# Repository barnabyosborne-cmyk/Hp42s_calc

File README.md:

# HP-42S clone — Plus42 on an ESP32-S3

An HP-42S-shaped calculator: e-paper display, LiPo cell, USB-C and BLE, a
custom keypad PCB with metal dome switches, a resin-printed case, running
[Plus42](https://thomasokken.com/plus42/) on an ESP32-S3.

Case dimensions follow the original HP-42S as closely as the parts allow:
**148 × 80 × 15 mm**.

## What is in here

| Path | What it is |
|---|---|
| `elec/src/*.ato` | The wiring, as [atopile](https://atopile.io) source. Compiles to a netlist. |
| `elec/footprints/hp42s.pretty/` | The footprints KiCad does not ship, generated by the two scripts in `tools/`. |
| `elec/layout/` | The KiCad project. Placement and routing live here. |
| `tools/gen_dome_footprints.py` | Parametric generator for the metal dome sites. |
| `tools/gen_ic_footprints.py` | The same for the regulator, the IR emitter, the status LED, the ESD array, the USB-C receptacle and the recovery buttons. |
| `docs/connections.md` | The connection table in prose, with the reasoning. |
| `docs/keypad-geometry.md` | The measured key grid, and the clearances that follow. |
| `docs/display-mounting.md` | The panel's tail and off-centre image, and where the cell can go. |
| `docs/front-face.md` | The etched metal plate, the window, and an edge-lit frontlight. |
| `docs/before-layout.md` | **What is still open, and whether it stops you starting.** |
| `docs/board-thickness.md` | Why the board is 1.6 mm, and flex under the keyboard. |
| `docs/layout-walkthrough.md` | **The layout, step by step.** Written for a first PCB. |
| `docs/pcb-process.md` | The map from netlist to boards in your hand. |
| `docs/kicad-setup.md` | Why the pin numbers are what they are. |
| `docs/breadboard.md` | What a XIAO ESP32-S3 and a spare Waveshare panel can and cannot prove. |
| `firmware/` | The Plus42 port. Not started. |
| `hardware/` | Case and keycap files. Barnaby's own CAD. |

## Building the netlist

```
pip install atopile        # 0.2.69 at time of writing
ato --non-interactive build
```

The flag goes before `build`, not after.

Output lands in `build/`: `default.net` (KiCad netlist), `default.csv` (BOM),
and a designator map. atopile does the wiring and the netlist; it does **not**
place or route. Layout stays in KiCad.

## Headline choices

- **MCU** — ESP32-S3-MINI-1-N8. The S3 over the C3/C6 because only the S3 has
  full USB OTG, which is what allows drag-and-drop file transfer as a mass
  storage device. The `-N8` specifically: it has no PSRAM, and octal PSRAM
  would eat GPIO33–37, where the panel interface lives.
- **Display** — Good Display GDEY0266T90, 2.66", 296 × 152 px in a 71.82 ×
  36.30 mm outline. Plus42 character cells are 6 × 8 px, rendered **2× across
  and 3× down**, giving **24 columns × 6 rows** at very close to the original
  42S's character size. The obvious 2.9" panel is 79.0 mm wide and will not
  fit an 80 mm shell. See `docs/character-size.md` for why the scaling is not
  square.
- **Power** — BQ25185 charger with power path → TPS63900 buck-boost to 3.3 V →
  MAX17048 fuel gauge. The buck-boost is mandatory: the panel's VCI cannot
  take 4.2 V.
- **Keypad** — 37 keys, 6 columns × 7 rows, no diodes. Columns sit on
  RTC-capable GPIOs and wake the chip from deep sleep via `ext1`, so there is
  no scanner IC and no standing current. The physical grid is measured off a
  real 42S and is not uniform: 12.5 mm columns on the function rows, 15 mm
  across the numeric block.
- **On and off are keys, not a switch.** `EXIT/ON` wakes it and shift-`EXIT`
  sleeps it, the way a real 42S works. There is no power slider: the 3.3 V rail
  is always up and "off" is deep sleep at about 21 µA. Driving row 6 alone and
  arming `ext1` on column 0 alone makes `EXIT/ON` the only key that can wake it.
  `docs/power-control.md`.
- **Single-sided assembly.** Every part the fab house solders is on the back of
  the board. The front carries the panel, the 38 dome sites and the frontlight
  sliver's lands, all fitted afterwards. `docs/top-edge.md`.
- **Battery life** — roughly **15 months** on the 1600 mAh cell that fits, at
  2 h/day and 1500 keystrokes. About 33 hours of continuous execution. The cell
  is 6 × 45 × 55 mm, in board X 14–69 and Y 13–58 on the back.

## What is not settled

- **The panel's 47 µH inductor.** Named (Sumida CDRH2D18) but still on a
  stand-in land pattern, because the drawing has not turned up.

## Licence

The Plus42 firmware is GPLv2, and that carries over: anyone given or sold a
unit has to be able to get the source. Worth deciding on before the firmware
lands here.

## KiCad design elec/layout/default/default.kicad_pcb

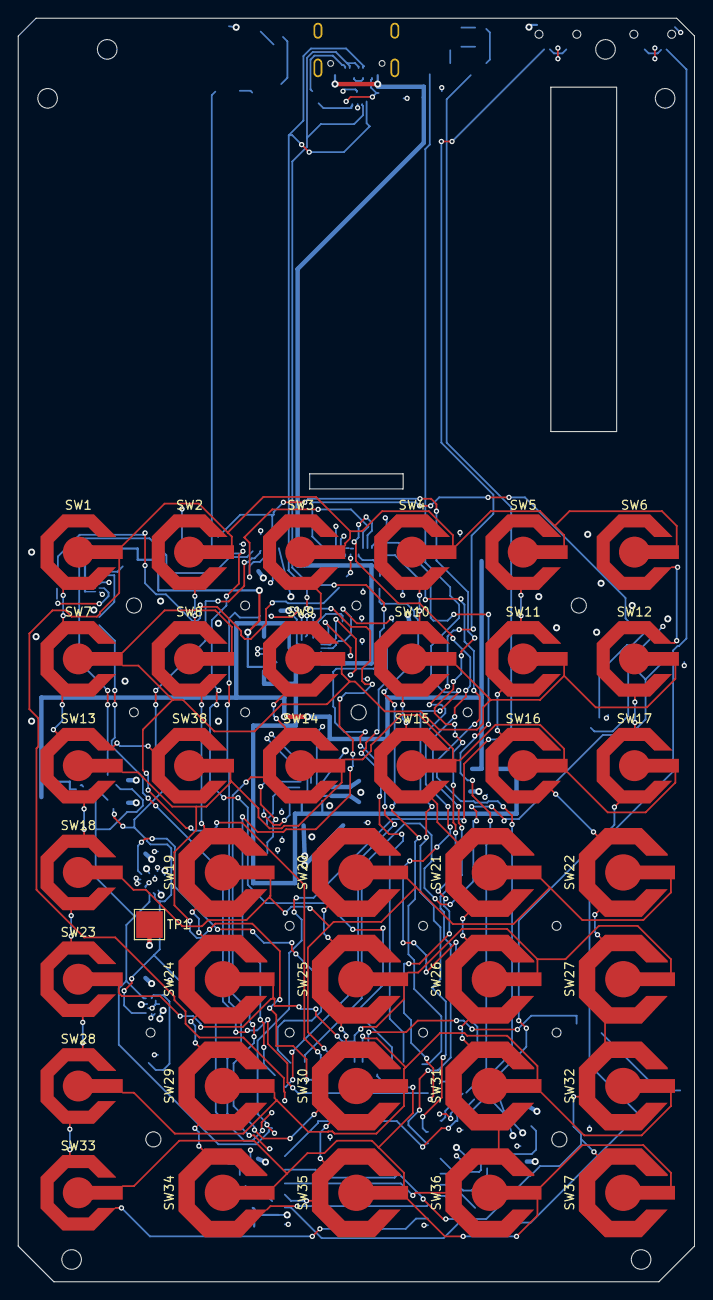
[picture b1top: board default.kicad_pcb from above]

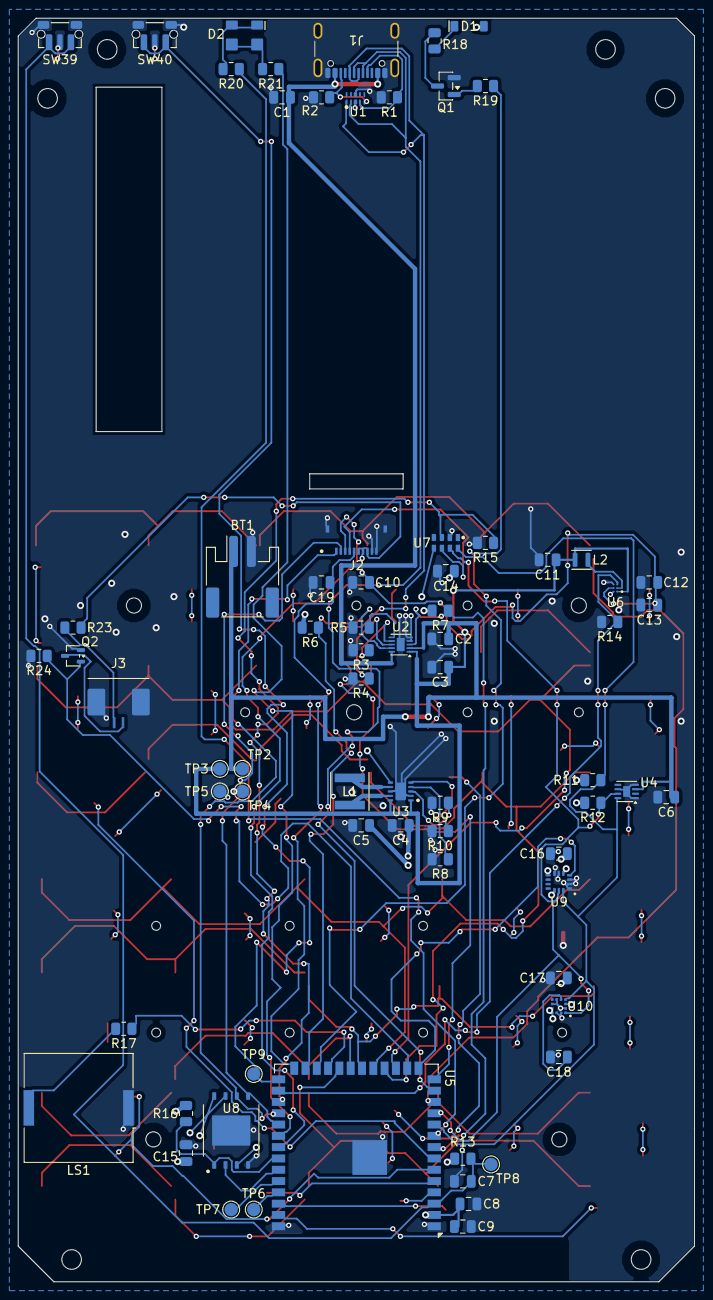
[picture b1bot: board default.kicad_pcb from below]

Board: 4 copper layers, 76.0 x 142.0 mm, 112 parts (73 on the bottom side), 64 nets.

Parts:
BT1: ?; JST_PH_S2B-PH-SM4-TB_1x02-1MP_P2.00mm_Horizontal
C1, C2, C3, C4, C5, C6, C7, C8, C9, C10, C11, C12, C13, C14, C15, C16, C17, C18, C19: ?; C_0805_2012Metric
D1: ?; Vishay_VSMB2943SLX01_SideView
D2: ?; XINGLIGHT_XL-C4040_SideView
J1: ?; USB_C_Receptacle_GCT_USB4105-xx-A_16P_TopMnt_Horizontal
J2: ?; Hirose_FH34SRJ-10S-0.5SH_1x10-1MP_P0.50mm_Horizontal
J3: ?; FPC_1.0mm_2P_TopContact_1.0K-LS
L1: ?; L_SXN_SMNR4020
L2: ?; L_Murata_DFE201610P
LS1: ?; Buzzer_Murata_PKLCS1212E
Q1: ?; SOT-23
Q2: ?; SOT-323_SC-70
R1, R2, R3, R4, R5, R6, R7, R8, R9, R10, R11, R12, R13, R14, R15, R16, R17, R18, R19, R20, R21, R23, R24: ?; R_0805_2012Metric
SW1, SW2, SW3, SW4, SW5, SW6, SW7, SW8, SW9, SW10, SW11, SW12, SW13, SW14, SW15, SW16, SW17, SW18, SW23, SW28, SW33, SW38: ?; Dome_4Leg_8.5mm
SW19, SW20, SW21, SW22, SW24, SW25, SW26, SW27, SW29, SW30, SW31, SW32, SW34, SW35, SW36, SW37: ?; Dome_4Leg_10mm
SW39, SW40: ?; Alps_SKRTLAE010_SidePush
TP1: ?; TestPoint_Pad_3.0x3.0mm
TP2, TP3, TP4, TP5, TP6, TP7, TP8, TP9: ?; TestPoint_Pad_D1.5mm
U1: ?; TI_DQA0010A_USON-10_2.5x1mm_P0.5mm
U2: ?; Texas_DSQ0010A_WSON-10-1EP_2x2mm_P0.4mm_EP0.9x1.5mm
U3: ?; TI_DSK0010A_WSON-10-1EP_2.5x2.5mm_P0.5mm_EP2x1.2mm
U4: ?; TDFN-8-1EP_2x2mm_P0.5mm_EP0.8x1.2mm
U5: ?; ESP32-S3-WROOM-1
U6: ?; TI_YFF0006_DSBGA-6_0.88x1.23mm_P0.4mm
U7: ?; MicroCrystal_C7_3.2x1.5mm_RV-8263
U8: ?; SPI_NAND_UPDFN-8_8x6mm_P1.27mm
U9: ?; ST_LGA-14L_3x2.5mm_P0.5mm
U10: ?; ST_LGA-12_2x2mm_P0.5mm

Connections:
bat: BT1.1, C2.1, C6.1, TP2.1, U2.2, U4.3
boot: SW40.1, TP9.1, U5.27
buzzer: R17.1, U5.23
c1: C18.1, U10.5
cathode: D1.1, R18.1
cc1: J1.A5, R1.1, U1.4
cc2: J1.B5, R2.1, U1.5
cfg1: R9.1, U3.3
cfg2: R10.1, U3.4
cfg3: R8.1, U3.5
chg_stat: R6.1, U2.9, U5.25
chg_stat2: R7.1, U2.3, U5.8
col0: SW1.1, SW7.1, SW13.1, SW18.1, SW23.1, SW28.1, SW33.1, SW38.1, U5.39
col1: SW2.1, SW8.1, SW19.1, SW24.1, SW29.1, SW34.1, U5.38
col2: SW3.1, SW9.1, SW14.1, SW20.1, SW25.1, SW30.1, SW35.1, U5.4
col3: SW4.1, SW10.1, SW15.1, SW21.1, SW26.1, SW31.1, SW36.1, U5.5
col4: SW5.1, SW11.1, SW16.1, SW22.1, SW27.1, SW32.1, SW37.1, U5.6
col5: SW6.1, SW12.1, SW17.1, U5.7
drain: Q1.3, R18.2
en: C7.1, R13.1, SW39.1, TP8.1, U5.3
extcomin: J2.4, U7.6
fl_a: J3.1, R23.2
fl_en: Q2.1, R24.1, U5.16
fl_k: J3.2, Q2.3
flash_cs: R16.1, U5.34, U8.1
flash_miso: U5.35, U8.2
gate: Q1.1, R19.2
gnd: BT1.2, C1.2, C2.2, C3.2, C4.2, C5.2, C6.2, C7.2, C8.2, C9.2, C10.2, C11.2, C12.2, C13.2, C14.2, C15.2, C16.2, C17.2, C18.2, C19.2, J1.A1, J1.A12, J1.B1, J1.B12, J1.SH, J2.9, J2.10, J2.MP, J3.MP, LS1.1, Q1.2, Q2.2, R1.2, R2.2, R3.2, R4.2, R5.2, R8.2, R9.2, R10.2, R14.2, R15.2, R24.2, SW39.2, SW39.MP, SW40.2, SW40.MP, TP1.1, TP5.1, U1.3, U1.8, U2.4, U2.5, U2.11, U3.2, U3.8, U3.11, U4.1, U4.4, U4.6, U4.9, U5.1, U5.40, U5.41, U6.A2, U6.C2, U7.2, U8.4, U8.9, U9.1, U9.2, U9.3, U9.6, U9.7, U10.2, U10.6, U10.8, U10.11, U10.12
i2c_scl: R12.1, U4.7, U5.11, U7.7, U9.13, U10.1
i2c_sda: R11.1, U4.8, U5.10, U7.8, U9.14, U10.4
ilim_vset: R3.1, U2.7
imu_int1: U5.15, U9.4
ir_led: R19.1, U5.24
iset: R4.1, U2.8
led_green: R21.1, U5.32
led_red: R20.1, U5.9
lx1: L1.1, U3.9
lx2: L1.2, U3.7
mip_clkoe: R15.1, U5.29, U7.3
mip_cs: J2.3, U5.33
mip_disp: C19.1, J2.5, U5.26
mip_mosi: J2.2, U5.31, U8.5
mip_pwr: R14.1, U5.28, U6.C1
mip_sck: J2.1, U5.30, U8.6
row0: SW1.2, SW2.2, SW3.2, SW4.2, SW5.2, SW6.2, U5.12
row1: SW7.2, SW8.2, SW9.2, SW10.2, SW11.2, SW12.2, U5.17
row2: SW13.2, SW14.2, SW15.2, SW16.2, SW17.2, SW38.2, U5.18
row3: SW18.2, SW19.2, SW20.2, SW21.2, SW22.2, U5.19
row4: SW23.2, SW24.2, SW25.2, SW26.2, SW27.2, U5.20
row5: SW28.2, SW29.2, SW30.2, SW31.2, SW32.2, U5.21
row6: SW33.2, SW34.2, SW35.2, SW36.2, SW37.2, U5.22
sounder: LS1.2, R17.2
sw5: L2.2, U6.B1
sys: C3.1, C11.1, L2.1, TP3.1, U2.1, U3.1, U3.10, U6.A1
t_green: D2.2, D2.4, R21.2
t_red: D2.1, D2.3, R20.2
ts_mr: R5.1, U2.6
uart0_rx: TP7.1, U5.36
uart0_tx: TP6.1, U5.37
usb_dm: J1.A7, J1.B7, U1.2, U5.13
usb_dp: J1.A6, J1.B6, U1.1, U5.14
v3v3: C4.1, C5.1, C8.1, C9.1, C14.1, C15.1, C16.1, C17.1, D1.2, R6.2, R7.2, R11.2, R12.2, R13.2, R16.2, TP4.1, U3.6, U5.2, U7.5, U8.3, U8.7, U8.8, U9.5, U9.8, U9.12, U10.3, U10.9, U10.10
v5: C10.1, C12.1, C13.1, J2.6, J2.7, J2.8, R23.1, U6.B2
vbus: C1.1, J1.A4, J1.A9, J1.B4, J1.B9, U2.10

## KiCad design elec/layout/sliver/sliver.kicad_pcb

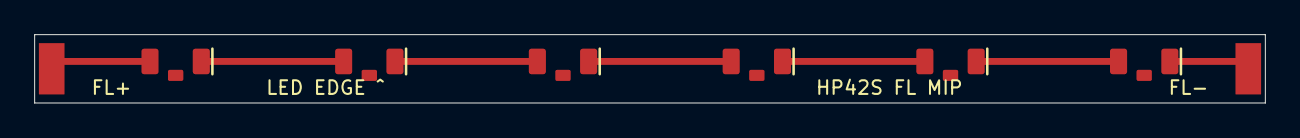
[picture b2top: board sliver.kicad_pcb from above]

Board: 2 copper layers, 72.0 x 4.0 mm, 8 parts (0 on the bottom side), 7 nets.

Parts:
D1, D2, D3, D4, D5, D6: 599-2Q01-147F; Dialight_599_White_1208_RA
TP1: FL+; Frontlight_SliverWirePad
TP2: FL-; Frontlight_SliverWirePad

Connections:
fb: D6.1, TP2.1
n1: D1.1, D2.2
n2: D2.1, D3.2
n3: D3.1, D4.2
n4: D4.1, D5.2
n5: D5.1, D6.2
vled: D1.2, TP1.1

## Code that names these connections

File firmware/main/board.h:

// board.h -- every pin on the HP-42S clone, in one place.
//
// These are not choices to make here. They come out of elec/src/hp42s.ato and
// are fixed by the schematic; docs/connections.md is the readable version of
// the same table. If a pin moves on the board it moves here, and nowhere else.
#pragma once

#include "driver/gpio.h"

// --- keypad: 6 columns x 7 rows, 37 keys, no diodes ------------------------
// Rows are driven, columns are read. Columns sit on RTC-capable GPIOs so they
// can wake the chip from deep sleep through ext1 with no scanner and no
// standing current; that is most of the battery life.
#define KP_COLS 6
#define KP_ROWS 7

static const gpio_num_t kp_col[KP_COLS] = {
    GPIO_NUM_1, GPIO_NUM_2, GPIO_NUM_4, GPIO_NUM_5, GPIO_NUM_6, GPIO_NUM_7,
};
static const gpio_num_t kp_row[KP_ROWS] = {
    GPIO_NUM_8,  GPIO_NUM_9,  GPIO_NUM_10, GPIO_NUM_11,
    GPIO_NUM_12, GPIO_NUM_13, GPIO_NUM_14,
};

// --- e-paper panel, GDEY0266T90 / SSD1680 ----------------------------------
#ifndef HP42S_WOKWI
#define EPD_CS   GPIO_NUM_33
#define EPD_DC   GPIO_NUM_34
#else
// The Wokwi simulation runs on an ESP32-S3-DevKitC-1, whose headers do not
// bring out GPIO 33 and 34 (the module uses them for octal PSRAM). Both are
// free pins on the real board, so the simulation borrows 40 and 42 instead.
// sim/wokwi/ builds with HP42S_WOKWI defined; nothing else ever should.
#define EPD_CS   GPIO_NUM_40
#define EPD_DC   GPIO_NUM_42
#endif
#define EPD_RST  GPIO_NUM_35
#define EPD_BUSY GPIO_NUM_36
#define EPD_SCK  GPIO_NUM_37
#define EPD_MOSI GPIO_NUM_38

// --- everything else -------------------------------------------------------
#define PIN_SOUNDER   GPIO_NUM_21   // 1k in series into the piezo element
#define PIN_IR_LED    GPIO_NUM_47   // FET gate, HP-82240 printing
#define PIN_LED_RED   GPIO_NUM_16   // common anode: LOW lights it
#define PIN_LED_GREEN GPIO_NUM_39
#define PIN_I2C_SDA   GPIO_NUM_17   // MAX17048 fuel gauge, 4k7 pull-ups
#define PIN_I2C_SCL   GPIO_NUM_18
#define PIN_CHG_STAT1 GPIO_NUM_48   // BQ25185, open drain, 100k pull-ups
#define PIN_CHG_STAT2 GPIO_NUM_15
#define PIN_BOOT      GPIO_NUM_0    // BOOT button and its test pad

// The status LED is common anode, so it lights on a LOW.
#define LED_ON  0
#define LED_OFF 1

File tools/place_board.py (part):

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    # faces the bay and the cell's leads run straight in without doubling
    # back. It moved right, out from under the charger, because the side-entry
    # part's courtyard is 9.2 x 10.2 mm against the vertical one's 6.9 x 5.5.
    # U2 keeps its place: C2 at its BAT pin and C3 at its SYS pin, with the
    # four programming resistors on its right-hand side where those pins are.
    "BT1": (50.8, 64.77, "B", 180),
    "U2":  (33.02, 72.39, "B", 0),
    "C2":  (28.575, 71.755, "B", 0),  # BAT, at U2 pin 2
    "C3":  (28.575, 74.93, "B", 0),   # SYS, at U2 pin 1
    "R7":  (28.575, 68.58, "B", 0),   # CHG_STAT2 pullup, at pin 3
    # 0805 since 25 October 2026: R3/R4/R5 one grid step further from U2
    # than the 0402s were, which keeps the same 1.7 mm channel between U2's
    # pins and the resistor pads, and R6 out past VBUS's descent at x 40.4.
    "R5":  (37.465, 70.485, "B", 0),   # TS_MR, at pin 6
    "R3":  (37.465, 73.025, "B", 0),   # ILIM_VSET, at pin 7
    "R4":  (37.465, 76.2, "B", 0),   # ISET, at pin 8
    "R6":  (43.18, 70.485, "B", 0),  # CHG_STAT pullup, at pin 9

    # -- BACK, Y 86..96, centre: the 3V3 regulator ---------------------------
    # L1 straddles the TPS63900's two switch pins. C4 and C5 are the output
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    # -- BACK, Y 87..91, left: the fuel gauge --------------------------------
    # The one analogue part on the board, so it is kept away from both
    # boosts: 14 mm below the display inductor and 45 mm from the
    # frontlight's. C6 is its BAT bypass, at pin 3; R11 and R12 pull the
    # I2C bus up, at pins 7 and 8.
    "U4":  (7.62, 88.9, "B", 0),
    "C6":  (3.175, 89.535, "B", 0),
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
